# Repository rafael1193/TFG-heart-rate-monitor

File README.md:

# Diseño de un pulsómetro por infrarrojos

Trabajo Fin de Grado consistente en diseñar un pulsómetro basado en pleistomografía con sensor infrarrojo.

## Estructura del repositorio

* `circuitos/`  Archivos CAD y CAM del proyecto
  - `circuitos/eagle/`  Esquema del circuito y diseño de la PCB, usando *Eagle*
  - `circuitos/kicad/`  Esquema del circuito auxiliar para programar el firmware durante la fase de prototipo, usando *KiCad*
  - `circuitos/spice/`  Esquemas de los filtros, usando *gschem*, y *netlist* para simulación con *ngspice*
* `data/`        Resultados en bruto de pruebas de validación y resultados de simulaciones
* `datasheets/`  Hojas de características
* `img/`         Imágenes usadas en la memoria
* `presentacion/` Presentación de la defensa
  - `presentacion/video/` Vídeo de demostración
* `report/`     Memoria del Trabajo Fin de Grado, fuentes para construirla y bibliografía
* `src/`        Código fuente
  - `src/Pulsometro`    Fuentes de la aplicación Pulsómetro para Android, usando Android Studio
  - `src/androidplot`   Referencia, `git submodule`, a las fuentes de la biblioteca *androidplot*.
  - `src/pulsometro.X`  Fuentes del firmware para el micocontrolador, usando MPLAB X

## Licencias/Licensing

 * circuitos/
 ``` 
    Copyright (C) 2015 Rafael Bailón-Ruiz
    
    This documentation describes Open Hardware and is licensed under the
    CERN OHL v. 1.2.
    
    You may redistribute and modify this documentation under the terms of the
    CERN OHL v.1.2. (http://ohwr.org/cernohl). This documentation is
    distributed WITHOUT ANY EXPRESS OR IMPLIED WARRANTY, INCLUDING OF
    MERCHANTABILITY, SATISFACTORY QUALITY AND FITNESS FOR A PARTICULAR PURPOSE.
    Please see the CERN OHL v.1.2 for applicable conditions.
 ```
 
 * data/
 ```
    Copyright (C) 2015  Rafael Bailón-Ruiz
    
    This work is licensed under the Creative Commons Attribution-ShareAlike 4.0
    International License. To view a copy of this license, visit 
    http://creativecommons.org/licenses/by-sa/4.0/.
 ```
 
 * img/
 ```
    Images with bibliography citation (/report/bibliography.bib) are property
    of their respective authors. Otherwise, images are own-work or come from
    public domain and the following copyright notice applies:
    
    Copyright (C) 2015  Rafael Bailón-Ruiz
    
    This work is licensed under the Creative Commons Attribution-ShareAlike 4.0
    International License. To view a copy of this license, visit 
    http://creativecommons.org/licenses/by-sa/4.0/.
 ```
 
 * presentacion/ & report/
 ```
    Copyright (C) 2015  Rafael Bailón-Ruiz
    
    This work is licensed under the Creative Commons Attribution-ShareAlike 4.0
    International License. To view a copy of this license, visit 
    http://creativecommons.org/licenses/by-sa/4.0/.
 ```
 
 * src/
 ```
    Pulsómetro
    Copyright (C) 2015  Rafael Bailón-Ruiz
    
    This program is free software: you can redistribute it and/or modify
    it under the terms of the GNU General Public License as published by
    the Free Software Foundation, either version 3 of the License, or
    (at your option) any later version.
    
    This program is distributed in the hope that it will be useful,
    but WITHOUT ANY WARRANTY; without even the implied warranty of
    MERCHANTABILITY or FITNESS FOR A PARTICULAR PURPOSE.  See the
    GNU General Public License for more details.
    
    You should have received a copy of the GNU General Public License
    along with this program.  If not, see <http://www.gnu.org/licenses/>.
 ```

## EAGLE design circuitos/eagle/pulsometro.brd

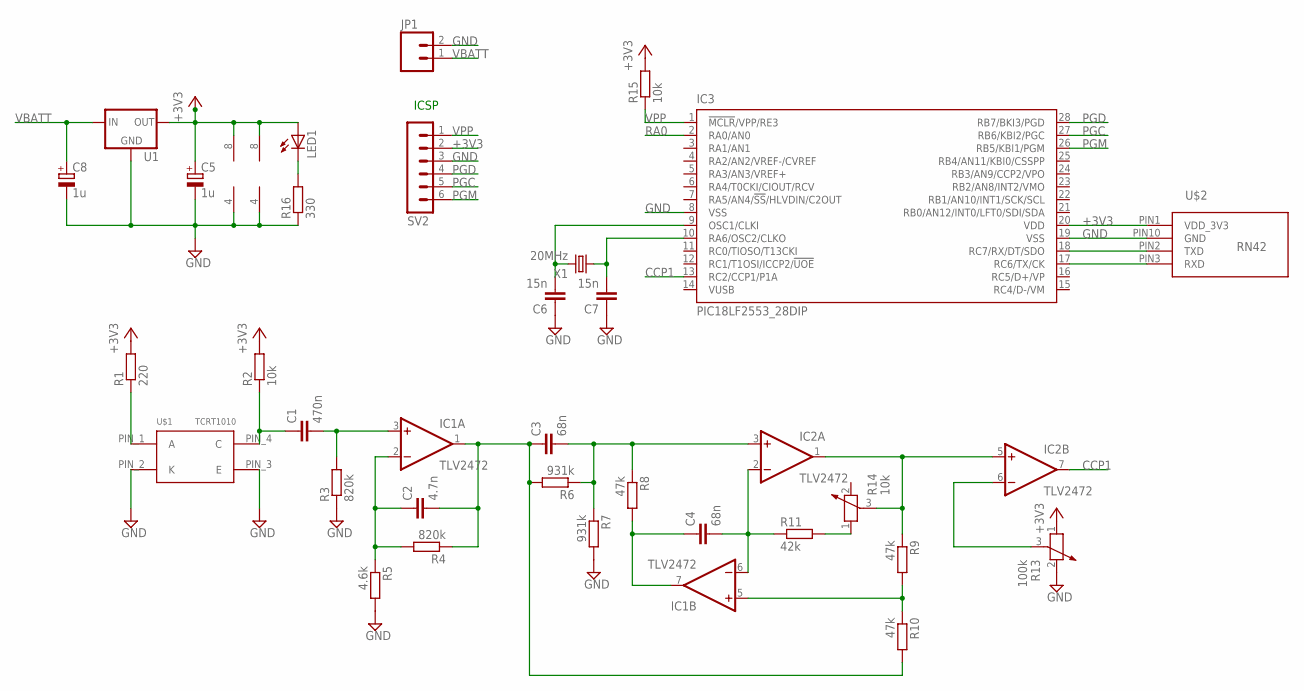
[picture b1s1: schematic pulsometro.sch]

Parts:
C1: 470n; C025-025X050
C2: 4.7n; C025-025X050
C3, C4: 68n; C025-025X050
C5, C8: 1u; E2,5-5
C6, C7: 15n; C025-025X050
IC1, IC2: TLV2472; DIL08
IC3: PIC18LF2553_28DIP; DIL28-3
JP1: M02PTH; 1X02
LED1: LED3MM
R1: 220; 0204/7
R2, R15: 10k; 0204/7
R3, R4: 820k; 0204/7
R5: 4.6k; 0204/7
R6, R7: 931k; 0204/7
R8, R9, R10: 47k; 0204/7
R11: 42k; 0204/7
R13: 100k; PT-10
R14: 10k; PT-10
R16: 330; 0204/7
SV2: MA06-1
U1: V_REG_78XXTO-92_UNTESTED; TO-92
U$1: TCRT1010
U$2: RN42; 2X10-2MMSOCKET
X1: 20MHz; HC49

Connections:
+3V3: C5.+, IC1.8 (V+), IC2.8 (V+), IC3.20 (VDD), LED1.A, R1.2, R2.2, R13.1, R15.2, SV2.2, U1.3 (OUT), U$2.PIN1 (VDD_3V3)
CCP1: IC2.7 (OUT), IC3.13 (RC2/CCP1/P1A)
GND: C5.-, C6.1, C7.1, C8.-, IC1.4 (V-), IC2.4 (V-), IC3.8 (VSS), IC3.19 (VSS), JP1.2, R3.1, R5.2, R7.2, R13.2, R16.1, SV2.3, U1.1 (GND), U$1.PIN_2 (K), U$1.PIN_3 (E), U$2.PIN10 (GND)
unnamed: R1.1, U$1.PIN_1 (A)
unnamed: C1.1, R2.1, U$1.PIN_4 (C)
unnamed: C2.1, IC1.2 (-IN), R4.2, R5.1
unnamed: C1.2, IC1.3 (+IN), R3.2
unnamed: C2.2, C3.1, IC1.1 (OUT), R4.1, R6.2, R10.2
unnamed: C3.2, IC2.3 (+IN), R6.1, R7.1, R8.1
unnamed: C4.1, IC1.7 (OUT), R8.2
unnamed: C4.2, IC1.6 (-IN), IC2.2 (-IN), R11.1
unnamed: R11.2, R14.1
unnamed: IC2.1 (OUT), IC2.5 (+IN), R9.1, R14.3
unnamed: IC1.5 (+IN), R9.2, R10.1
unnamed: IC2.6 (-IN), R13.3
unnamed: IC3.18 (RC7/RX/DT/SDO), U$2.PIN2 (TXD)
unnamed: IC3.17 (RC6/TX/CK), U$2.PIN3 (RXD)
unnamed: LED1.K (C), R16.2
unnamed: C7.2, IC3.10 (RA6/OSC2/CLKO), X1.1
unnamed: C6.2, IC3.9 (OSC1/CLKI), X1.2
PGC: IC3.27 (RB6/KBI2/PGC), SV2.5
PGD: IC3.28 (RB7/BKI3/PGD), SV2.4
PGM: IC3.26 (RB5/KBI1/PGM), SV2.6
RA0: IC3.2 (RA0/AN0)
VBATT: C8.+, JP1.1, U1.2 (IN)
VPP: IC3.1 (!MCLR!/VPP/RE3), R15.1, SV2.1

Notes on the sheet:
ICSP

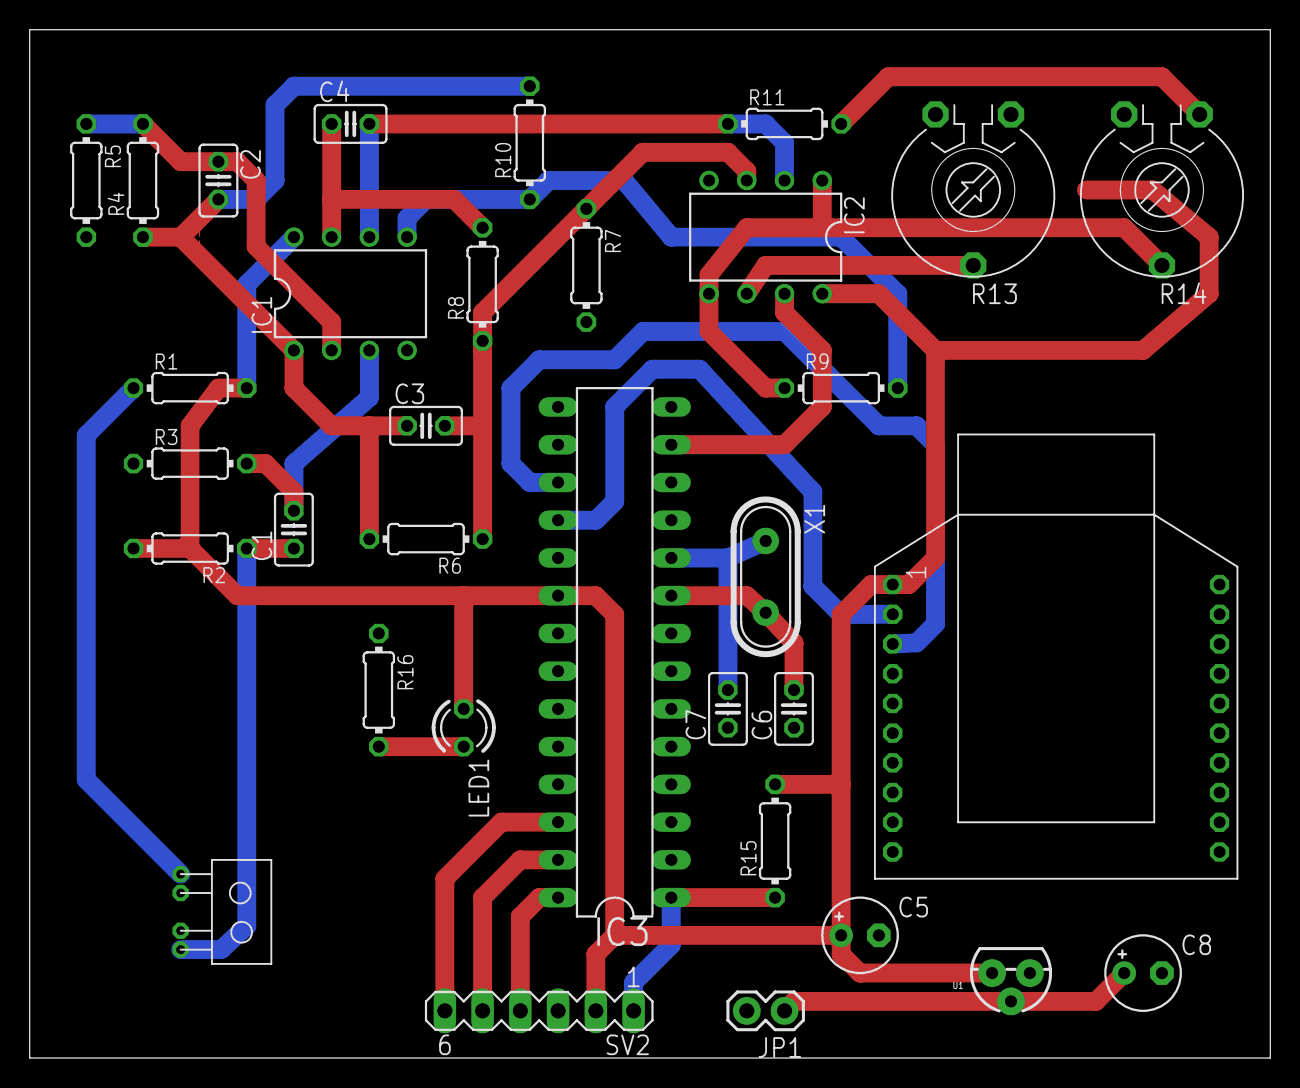
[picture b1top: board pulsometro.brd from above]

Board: 2 copper layers, 83.5 x 69.2 mm, 33 parts (0 on the bottom side), 25 nets.

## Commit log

2015-05-01 Update README.md
    Fix formatting typo.
2015-05-04 Enable and configure timer0 for 1s period pulse
2015-05-04 Add CCP application notes
2015-05-08 Measure period of input signal at pin 13.
    - Configure CCP module in "Capture" mode.
    - Configure Timer1 to measure time between CCP events
2015-05-19 Add GNU GPLv3 header.
2015-05-28 Change SYS_FREQ value to 20MHz
2015-05-28 OSCCON register definition is not needed.
2015-06-11 Fix high-pass filter resistance vale
    Was 82K instead of 820K
2015-06-11 Create app icon
2015-06-11 Initial code for android app
2015-06-15 Import RN41 bluetooth module datasheet
2015-06-16 Move KiCad files to *kicad* folder
2015-06-16 Add PCB made with eagle
2015-06-16 Import androidplot library
2015-06-17 Define plot component
2015-06-17 Declare bluetooth permissions
2015-06-24 Add PIC18LF2553 build target
2015-06-24 Configure UART communication
2015-06-24 Send value over UART at interval
    A fixed value is sent for now. In the future, it is going be BPM value.
2015-06-24 Declare variables as volatile
    Because they are modified by ISRs
2015-06-24 Add MCP1700 datasheet
2015-06-24 Add microchip libraries documentation
2015-06-24 Add RN-42 product user manual
2015-06-24 Add TLV2472 datasheet
2015-06-24 Import BluetoothChatService from Android examples
2015-06-24 Rename BluetoothChatService to BluetoothCommunicationService
2015-06-24 Import more files from Android example
2015-06-24 Add GPLv3+ license headers
2015-06-24 Fix missing import
2015-06-25 Fix reset timer1 values before using them
2015-06-25 Increase send time
2015-06-25 Calculate and send BPM as byte
2015-06-25 Several fixes in BPM calculation
    * BPM calculation formula was wrong and has been corrected.
    * Discard not valid _period_ values
    * Increase BPM value emission period
2015-06-26 Rebase Pulsometro app over BluetoothChat android example
2015-06-26 Change border color
2015-06-26 Display BPM placeholder
2015-06-26 Convert received byte from bluetooth to "unsigned" intger
2015-06-26 Fix xliff replacement
2015-06-26 Remove intermediate variables
2015-06-26 Send 0 from pulsemeter when pulses are not in valid interval
    This helps android app to detect whether finger is put
2015-06-26 Show figure dashes (U+2012) when no BPM value is available
2015-06-27 Implement plot
2015-06-28 Translate strings to Spanish
2015-06-28 Remove Log Fragment from Main Activiy
2015-06-28 Remove menu items
2015-06-28 Clean BluetoothChatFragment.java code
2015-06-28 Increase plot texts sizes and margins
2015-06-28 Translate toast messages to Spanish
2015-06-28 Set android:stackFromBottom="false" at activity_device_list
2015-06-28 Rename BluetoothChatFragment to PulseMeterDisplayFragment
2015-06-28 Use mean of recieved values as bpm datum
2015-06-29 Reduce amplifier resistor
2015-06-29 Add regulator to schematic and board
2015-06-29 Add report .gitignore
2015-06-29 Comienzo del informe
2015-06-29 Add system diagram
2015-07-01 Add Android app screenshot
2015-07-01 Update circuit
    * Remove transistor switch of TCRT1010 diode and change resistor value
    * Change LM358 op-amp to TLV2472
2015-07-01 Add circuit image
2015-07-01 Write some hardware chapters
2015-07-01 Fix voltage source value
2015-07-01 Refactor pulsometro.X code
2015-07-01 Add circuit images
2015-07-01 Add RN-42 Bluetooth module photo
2015-07-01 Add initial BibLaTeX bibliography
2015-07-01 Complete Hardware and Firmware sections
2015-07-04 Add new images
2015-07-04 Add compulsory annexes
2015-07-04 Fix pic firmware build
2015-07-04 Add validation test data
2015-07-04 Refactor pulsometro app
2015-07-04 Update bibliography
2015-07-04 More chapters written in report
2015-07-05 Include pcb in report
2015-07-07 Add images
2015-07-07 Complete more chapter 2 sections
2015-07-07 Translate "List of Listings"
2015-07-07 Rename "Cuadro" to "Tabla"
2015-07-07 Several changes
    * Rename "Nomenclatura" to "Glosario"
    * Fix some mistakes
    * Add "Anexos"
2015-07-07 Rename "Listado" to "Código" and move them to "Anexo II"
2015-07-07 Update UGR logo
2015-07-07 Update logo on mandatory pages
2015-07-07 Add box to circuit
2015-07-07 Move PCB to annex
2015-07-07 Remove background from component images
2015-07-07 Add simulations of filter stages
2015-07-07 Update report file
2015-07-09 Add more images
2015-07-09 Update compulsory annexes
2015-07-09 Remove void file
2015-07-09 Add final version of report
2015-07-12 Update gerber files
2015-07-12 Update project description
2015-07-12 Clarify /img copyright
2015-07-12 Explain repository strucutre
2015-07-12 Fix broken PDF
2015-07-16 Add new images for presentacion
2015-07-16 Add presentation
2015-07-20 Minor changes in presentation
2015-07-20 Fix typos
2015-07-21 Add demo video
2015-07-22 Update README.md
    * Add `presentacion/` instructions and license
    * Fix `report/` license

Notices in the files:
parts and their libraries:
SparkFun-Connectors: Licensing: Creative Commons ShareAlike 4.0 International - https://creativecommons.org/licenses/by-sa/4.0
